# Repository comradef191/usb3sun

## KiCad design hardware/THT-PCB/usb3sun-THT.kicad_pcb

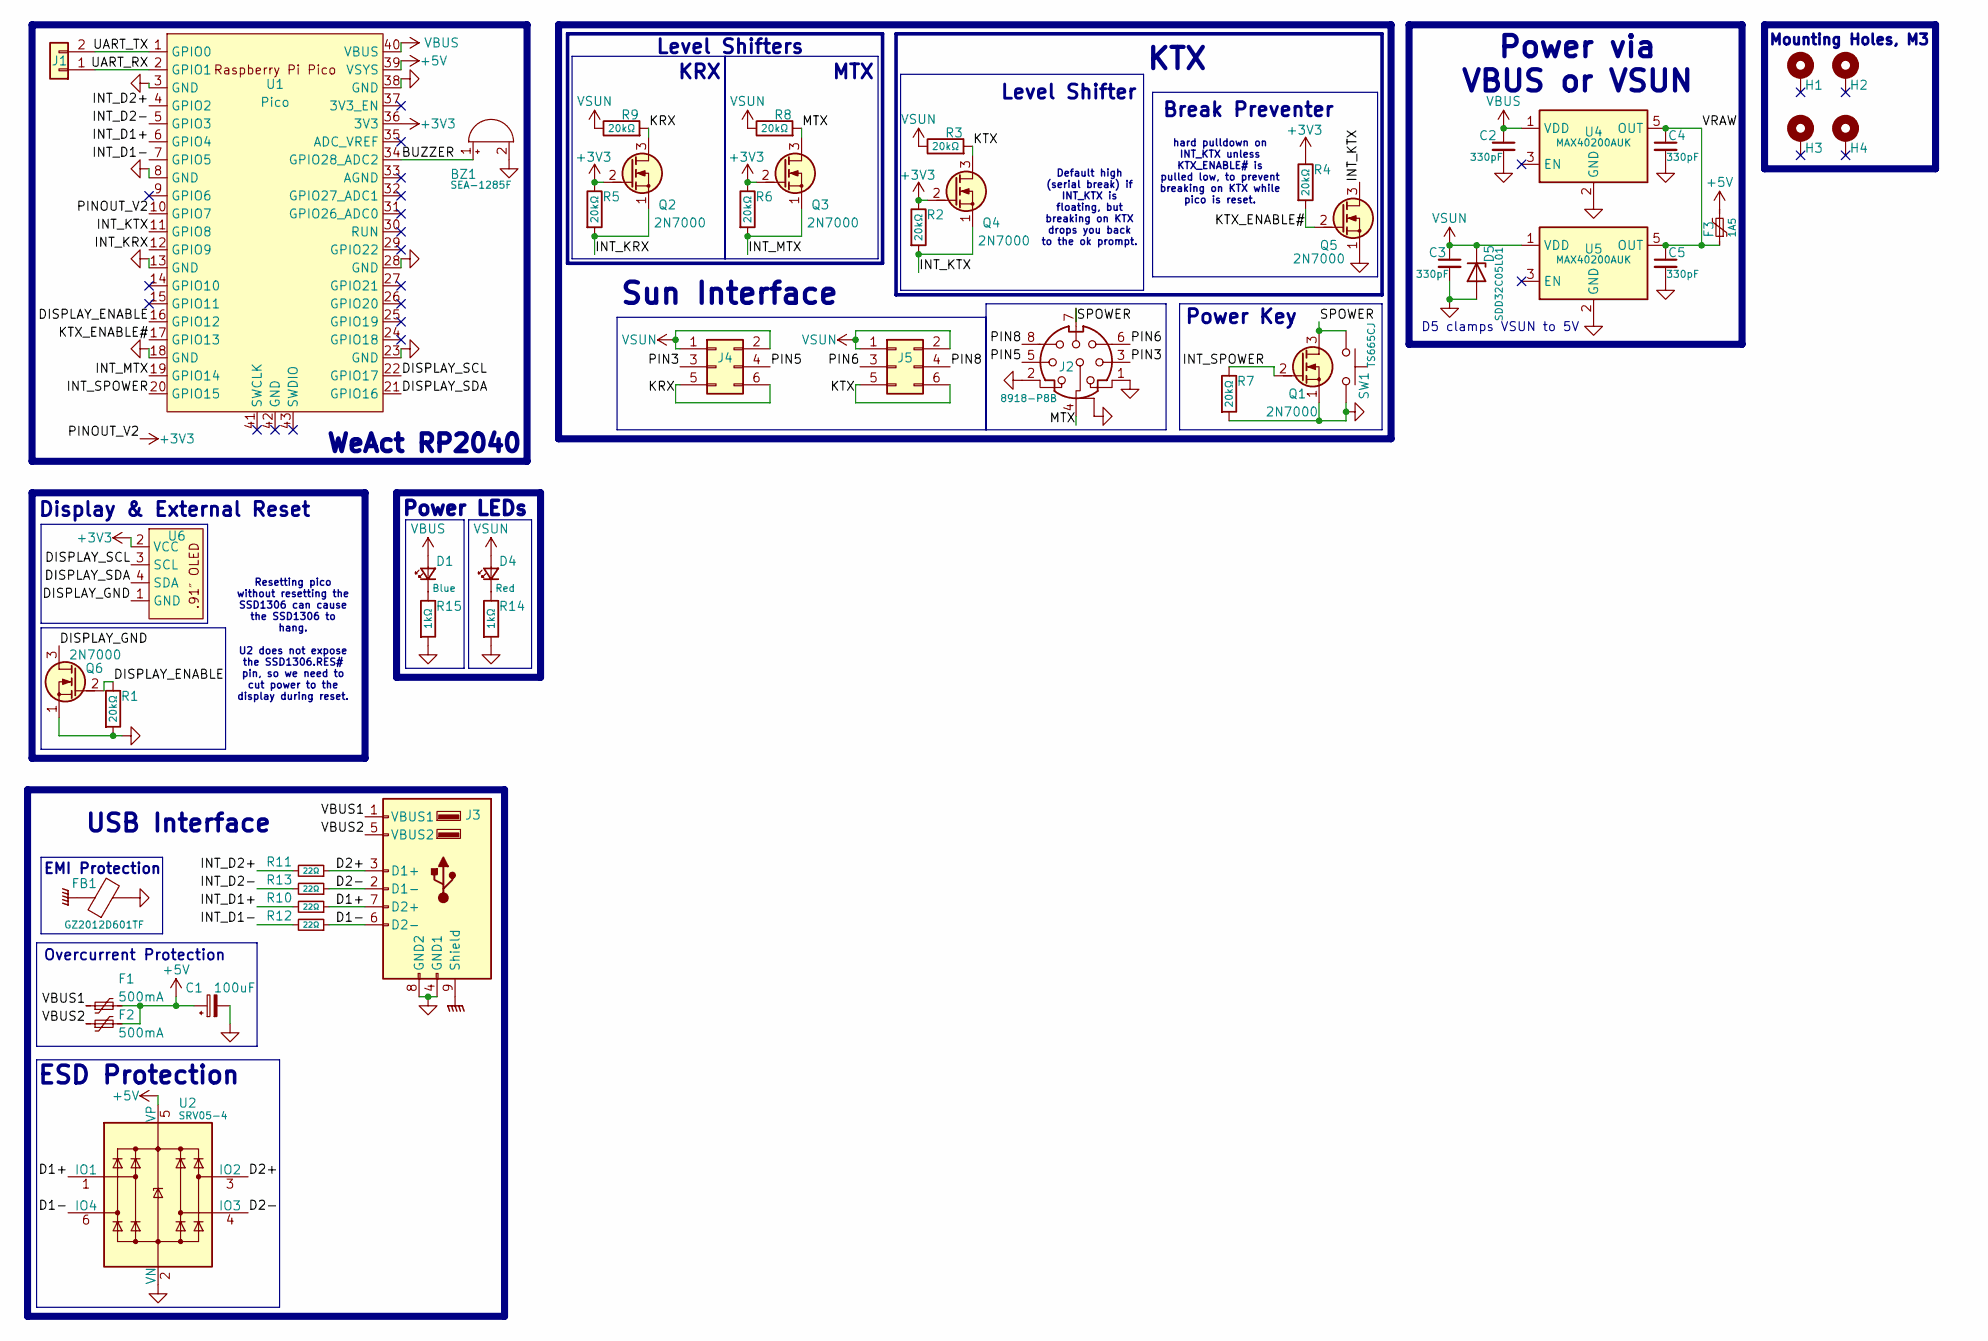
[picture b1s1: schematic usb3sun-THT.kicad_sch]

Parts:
BZ1: SEA-1285F; Buzzer_12x9.5RM7.6; LCSC C2693577
C1: 100uF; CP_EIA-3528-21_Kemet-B; LCSC C16133
C2, C3, C4, C5: 330pF; C_Disc_D3.8mm_W2.6mm_P2.50mm; LCSC C94711
D1: LED_D3.0mm; LCSC C2895474
D4: LED_D3.0mm; LCSC C440523
D5: SDD32C05L01; D_SOD-323_HandSoldering; LCSC C313311
F1, F2: 500mA; Fuse_1206_3216Metric; LCSC C70076
F3: 1A5; Fuse_1206_3216Metric; LCSC C70084
FB1: GZ2012D601TF; L_0805_2012Metric; LCSC C1017
H1, H2, H3, H4: MountingHole; MountingHole_3.2mm_M3_DIN965_Pad_TopBottom
J1: Conn_01x02; PinHeader_1x02_P2.54mm_Vertical
J2: 8918-P8B; Altronics_P1108_8918-P8B
J3: USB-U267-BWS; USB_A_CUI_UJ2-ADH-TH_Horizontal_Stacked; LCSC C2962392
J4, J5: Conn_02x03_Odd_Even; PinHeader_2x03_P2.54mm_Vertical
Q1, Q2, Q3, Q4, Q5, Q6: 2N7000; TO-92_Inline; LCSC C9114
R1, R2, R3, R4, R5, R6, R7, R8, R9: 20kΩ; R_Axial_DIN0207_L6.3mm_D2.5mm_P10.16mm_Horizontal
R10, R11, R12, R13: 22Ω; R_Axial_DIN0207_L6.3mm_D2.5mm_P10.16mm_Horizontal
R14, R15: 1kΩ; R_Axial_DIN0207_L6.3mm_D2.5mm_P10.16mm_Horizontal
SW1: TS665CJ; SW_PUSH_6mm_H4.3mm; LCSC C5340136
U1: Pico; Pico-BlackPill_Textless
U2: SRV05-4; SOT-23-6-routable; LCSC C85364
U4, U5: MAX40200AUK; SOT-23-5_HandSoldering; LCSC C2649430
U6: SSD1306-0.91-OLED-4pin-128x32

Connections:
+3V3: Q2.2 (G), Q3.2 (G), Q4.2 (G), R2.1, R4.1, R5.1, R6.1, U1.10 (GPIO7), U1.36 (3V3), U6.2 (VCC)
+5V: C1.1, F1.2, F2.2, F3.2, U1.39 (VSYS), U2.5 (VP)
/BUZZER: BZ1.1 (-), U1.34 (GPIO28_ADC2)
/D1+: J3.7 (D2+), R10.1, U2.1 (IO1)
/D1-: J3.6 (D2-), R12.1, U2.6 (IO4)
/D2+: J3.3 (D1+), R11.1, U2.3 (IO2)
/D2-: J3.2 (D1-), R13.1, U2.4 (IO3)
/DISPLAY_ENABLE: Q6.2 (G), R1.1, U1.16 (GPIO12)
/DISPLAY_GND: Q6.3 (D), U6.1 (GND)
/DISPLAY_SCL: U1.22 (GPIO17), U6.3 (SCL)
/DISPLAY_SDA: U1.21 (GPIO16), U6.4 (SDA)
/INT_D1+: R10.2, U1.6 (GPIO4)
/INT_D1-: R12.2, U1.7 (GPIO5)
/INT_D2+: R11.2, U1.4 (GPIO2)
/INT_D2-: R13.2, U1.5 (GPIO3)
/INT_KRX: Q2.1 (S), R5.2, U1.12 (GPIO9)
/INT_KTX: Q4.1 (S), Q5.3 (D), R2.2, U1.11 (GPIO8)
/INT_MTX: Q3.1 (S), R6.2, U1.19 (GPIO14)
/INT_SPOWER: Q1.2 (G), R7.1, U1.20 (GPIO15)
/KRX: J4.5, J4.6, Q2.3 (D), R9.2
/KTX: J5.5, J5.6, Q4.3 (D), R3.2
/KTX_ENABLE#: Q5.2 (G), R4.2, U1.17 (GPIO13)
/MTX: J2.4, Q3.3 (D), R8.2
/PIN3: J2.3, J4.3
/PIN5: J2.5, J4.4
/PIN6: J2.6, J5.3
/PIN8: J2.8, J5.4
/SPOWER: J2.7, Q1.3 (D), SW1.2
/UART_RX: J1.1, U1.2 (GPIO1)
/UART_TX: J1.2, U1.1 (GPIO0)
/VBUS1: F1.1, J3.1 (VBUS1)
/VBUS2: F2.1, J3.5 (VBUS2)
/VRAW: C4.1, C5.1, F3.1, U4.5 (OUT), U5.5 (OUT)
GND: BZ1.2 (+), C1.2, C2.2, C3.2, C4.2, C5.2, D5.2 (A), FB1.2, J2.1, J2.2, J2.SHIELD, J3.4 (GND1), J3.8 (GND2), Q1.1 (S), Q5.1 (S), Q6.1 (S), R1.2, R7.2, R14.2, R15.2, SW1.1, U1.3 (GND), U1.8 (GND), U1.13 (GND), U1.18 (GND), U1.23 (GND), U1.28 (GND), U1.38 (GND), U2.2 (VN), U4.2 (GND), U5.2 (GND)
GNDPWR: FB1.1, J3.9 (Shield)
unnamed: D1.1 (K), R15.1
unnamed: D4.1 (K), R14.1
VBUS: C2.1, D1.2 (A), U1.40 (VBUS), U4.1 (VDD)
VSUN: C3.1, D4.2 (A), D5.1 (K), J4.1, J4.2, J5.1, J5.2, R3.1, R8.1, R9.1, U5.1 (VDD)

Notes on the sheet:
Default high (serial break) if INT_KTX is floating, but breaking on KTX drops you back to the ok prompt.
hard pulldown on INT_KTX unless KTX_ENABLE# is pulled low, to prevent breaking on KTX while pico is reset.
Resetting pico without resetting the SSD1306 can cause the SSD1306 to hang. U2 does not expose the SSD1306.RES# pin, so we need to cut power to the display during reset.
KTX
WeAct RP2040
Mounting Holes, M3
Break Preventer
Overcurrent Protection
ESD Protection
Sun Interface
EMI Protection
Power Key
Power via VBUS or VSUN
Display & External Reset
USB Interface
KRX
D5 clamps VSUN to 5V
Level Shifters
MTX
Level Shifter
Power LEDs

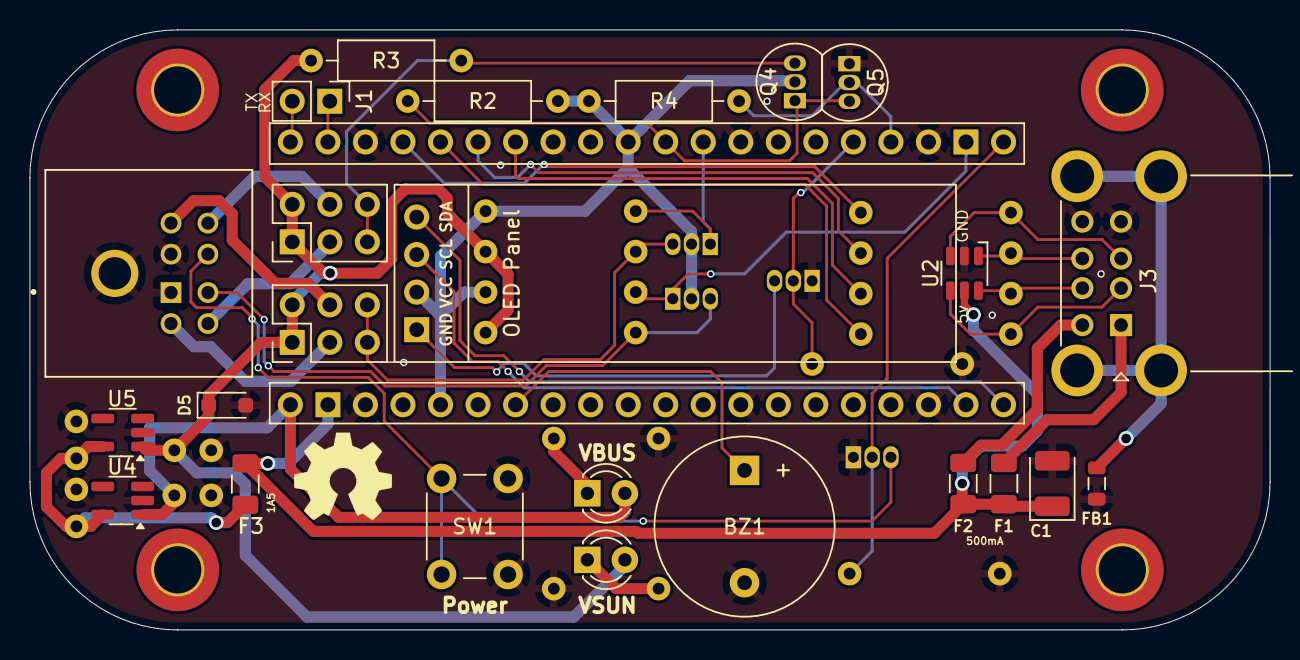
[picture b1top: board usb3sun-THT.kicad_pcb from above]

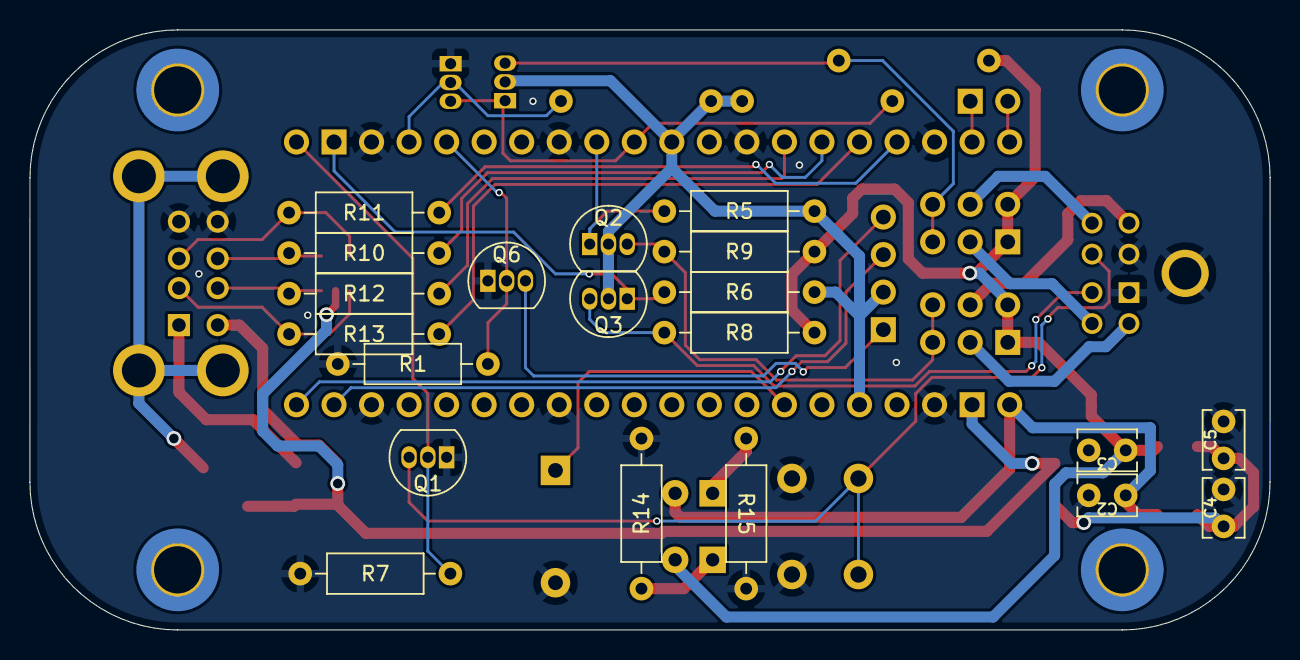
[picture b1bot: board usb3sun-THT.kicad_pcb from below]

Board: 2 copper layers, 83.9 x 40.6 mm, 49 parts (21 on the bottom side), 39 nets.

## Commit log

2024-03-10 Initial KiCAD Files
2024-03-10 Initial Schematic Copy & Organisation Removed redundant reset switch Removed redundant USB port Removed redundant Debug Header
2024-03-10 Change fets to match original refs
2024-03-10 SCH Complete; Begin PCB work!
2024-03-10 Simplification of LED circuits
2024-03-10 SCH Improvements
2024-03-28 Complete PCB layout, Further schematic adjustments; TODO traces
2024-03-29 Fully Routed
2024-03-29 Cleanup, Footprint location reshuffling
2024-03-29 Misc
2024-03-29 Add UART Header
2024-04-11 PCB work
2024-04-11 Fix Sun connector, add connector config jumpers
